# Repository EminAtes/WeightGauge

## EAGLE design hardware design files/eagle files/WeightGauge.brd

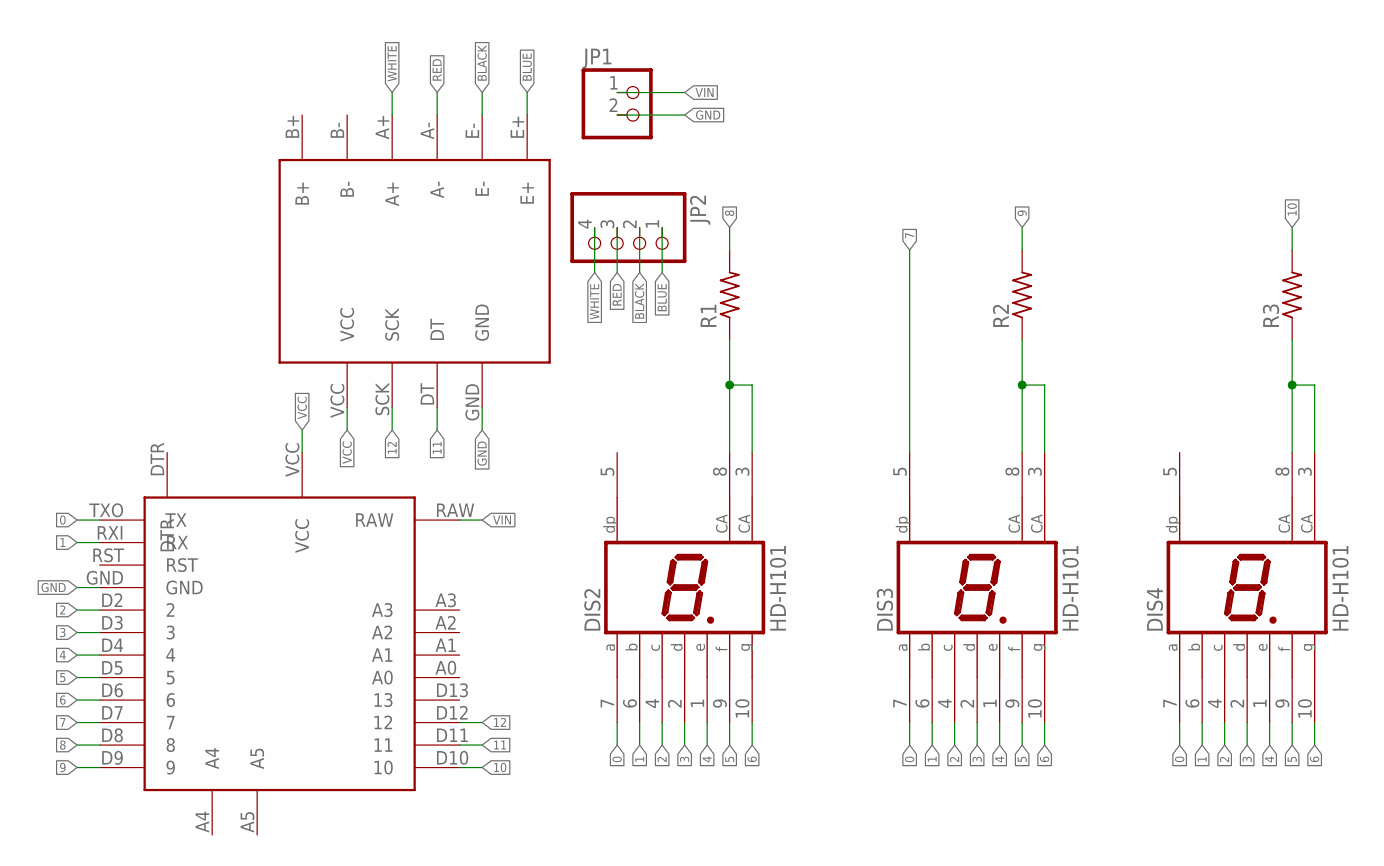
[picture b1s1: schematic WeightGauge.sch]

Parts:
DIS2, DIS3, DIS4: HD-H101; HDSP-M
JP1: PINHD-1X2/90; 1X02/90
JP2: PINHD-1X4/90; 1X04/90
R1, R2, R3: R-US_R1206; R1206
U$1: ARDUINO_PRO_MINI
U$2: HX711

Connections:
0: DIS2.7 (A), DIS3.7 (A), DIS4.7 (A), U$1.TXO (TX)
1: DIS2.6 (B), DIS3.6 (B), DIS4.6 (B), U$1.RXI (RX)
2: DIS2.4 (C), DIS3.4 (C), DIS4.4 (C), U$1.D2 (2)
3: DIS2.2 (D), DIS3.2 (D), DIS4.2 (D), U$1.D3 (3)
4: DIS2.1 (E), DIS3.1 (E), DIS4.1 (E), U$1.D4 (4)
5: DIS2.9 (F), DIS3.9 (F), DIS4.9 (F), U$1.D5 (5)
6: DIS2.10 (G), DIS3.10 (G), DIS4.10 (G), U$1.D6 (6)
7: DIS3.5 (DP), U$1.D7 (7)
8: R1.2, U$1.D8 (8)
9: R2.2, U$1.D9 (9)
10: R3.2, U$1.D10 (10)
11: U$1.D11 (11), U$2.DT
12: U$1.D12 (12), U$2.SCK
BLACK: JP2.2, U$2.E-
BLUE: JP2.1, U$2.E+
GND: JP1.2, U$1.GND, U$2.GND
unnamed: DIS2.3 (CA), DIS2.8 (CA), R1.1
unnamed: DIS3.3 (CA), DIS3.8 (CA), R2.1
unnamed: DIS4.3 (CA), DIS4.8 (CA), R3.1
RED: JP2.3, U$2.A-
VCC: U$1.VCC, U$2.VCC
VIN: JP1.1, U$1.RAW
WHITE: JP2.4, U$2.A+

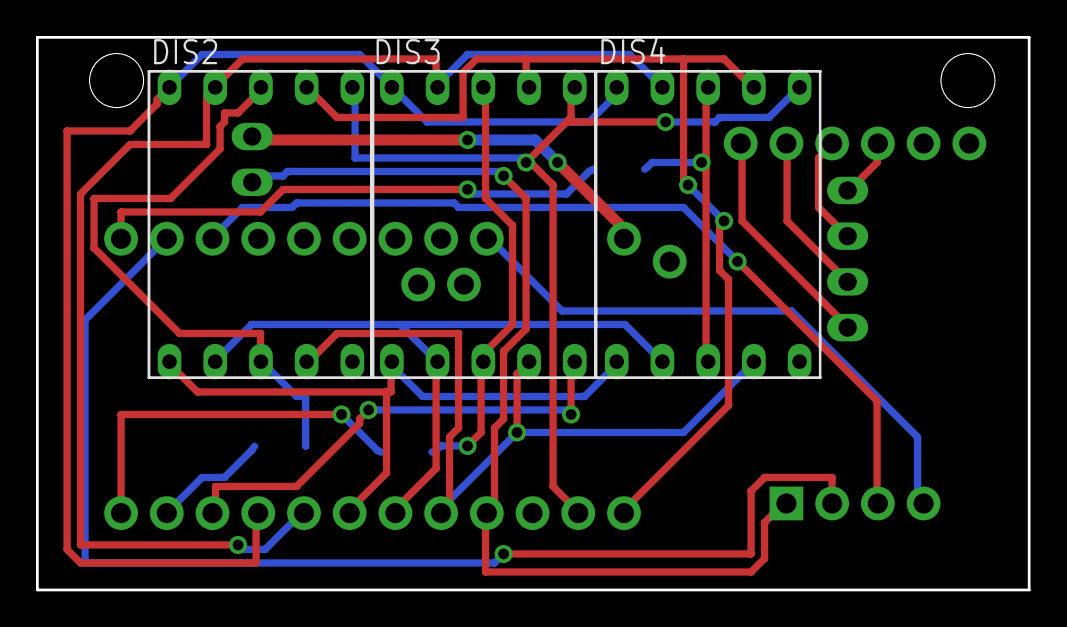
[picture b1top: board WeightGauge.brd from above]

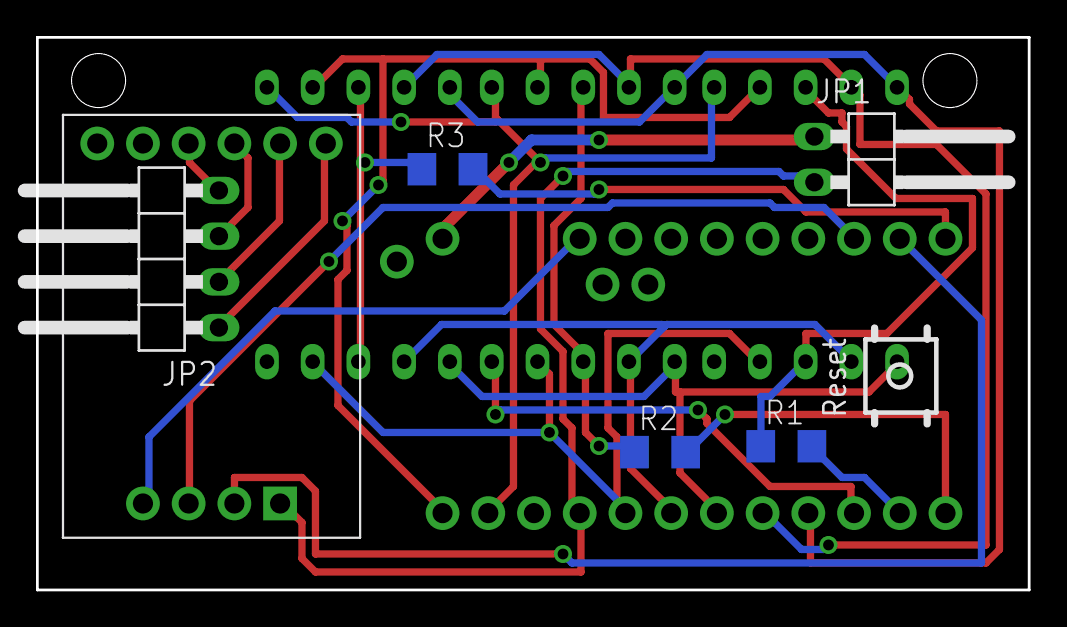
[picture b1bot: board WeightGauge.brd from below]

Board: 2 copper layers, 55.1 x 30.7 mm, 10 parts (7 on the bottom side), 23 nets.

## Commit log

2019-02-16 Commit Stage
    Commit Stage
